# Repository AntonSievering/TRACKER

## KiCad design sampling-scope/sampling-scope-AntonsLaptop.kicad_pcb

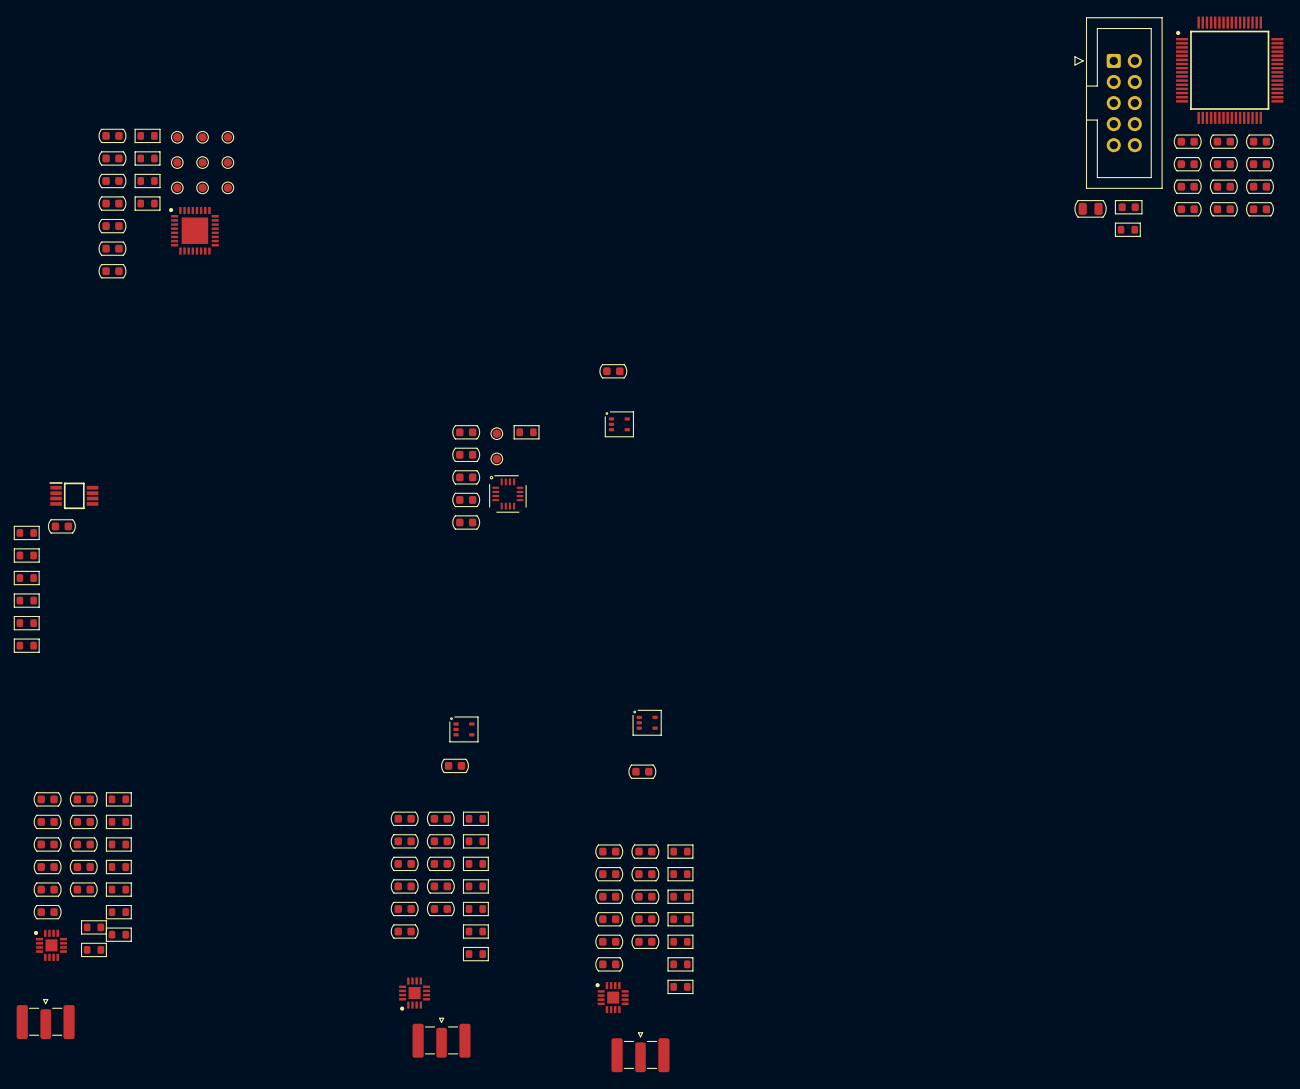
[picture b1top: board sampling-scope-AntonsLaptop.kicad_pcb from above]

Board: 4 copper layers, 123 parts (0 on the bottom side), 54 nets, no tracks yet.

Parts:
C1, C2, C7, C8, C11, C12, C13, C14, C15, C16, C19, C20, C21, C24, C25, C26, C27, C28, C29, C32, C36, C37, C38, C39, C44, C45, C46, C47, C48, C49, C54, C55, C56, C57, C58, C59, C62: 100n; C_0603_1608Metric
C3, C4, C5, C6, C33, C34, C35: 10n; C_0603_1608Metric
C9, C10, C17, C18, C22, C23, C30, C31, C43, C50, C51, C52, C53, C60, C61: 1u; C_0603_1608Metric
C40, C41: 2u2; C_0603_1608Metric
C42: 10u; C_0805_2012Metric
FB1: 1k@100MHz; L_0603_1608Metric
IC1: SY89296UMG; QFN50P500X500X90-33N-D
IC2, IC4, IC6: ADCMP582; QFN50P300X300X80-17N-D
IC3: SY10EP51VKG; SOP65P490X110-8N
IC5: STM32H562RGT6; QFP50P1200X1200X160-64N
J1, J2, J3: SMA; SMA_Edge_Mount
J4: Conn_02x05_Counter_Clockwise; IDC-Header_2x05_P2.54mm_Vertical
R1, R3, R6, R8, R10, R21, R23, R25, R30, R32, R34: 127; R_0603_1608Metric
R2, R4, R7, R9, R11, R22, R24, R26, R31, R33, R35: 82.5; R_0603_1608Metric
R5, R12, R13, R14, R15, R16, R17, R18, R19, R20, R28, R29: 0; R_0603_1608Metric
R27: 49R9; R_0603_1608Metric
TP1, TP2, TP3, TP4, TP5, TP6, TP7, TP8, TP9, TP10, TP11: TestPoint; TestPoint_Pad_D1.0mm
U1, U2, U4: LMV331; SOT-353_SC-70-5
U3: SY89831U; QFN-16_3x3mm_P0.5mm

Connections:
+3.3V: C1.1, C2.1, C3.1, C4.1, C5.1, C6.1, C7.1, C8.1, C15.1, C16.1, C18.1, C19.1, C20.1, C21.1, C28.1, C29.1, C31.1, C32.1, C33.1, C34.1, C35.1, C36.1, C37.1, C38.1, C42.1, C43.1, C44.1, C45.1, C46.1, C47.1, C48.1, C50.1, C58.1, C59.1, C61.1, C62.1, FB1.2, IC1.13 (VCC), IC1.18 (VCC), IC1.19 (VCC), IC1.22 (VCC), IC2.9 (V_{CCO}), IC2.12 (V_{CCO}), IC3.8 (VCC), IC4.9 (V_{CCO}), IC4.12 (V_{CCO}), IC5.1 (VBAT), IC5.19 (VDD_1), IC5.32 (VDD_2), IC5.48 (VDD_3), IC5.64 (VDD_4), IC6.9 (V_{CCO}), IC6.12 (V_{CCO}), R1.1, R3.1, R6.1, R8.1, R10.1, R12.1, R15.1, R21.1, R23.1, R25.1, R30.1, R32.1, R34.1, U1.5 (V+), U2.5 (V+), U3.7 (VCC), U3.14 (VCC), U4.5 (V+)
+5VA: C10.1, C12.1, C14.1, C23.1, C25.1, C27.1, C53.1, C55.1, C57.1, IC2.5 (VCCI), IC2.16 (VCCI), IC4.5 (VCCI), IC4.16 (VCCI), IC6.5 (VCCI), IC6.16 (VCCI)
-5VA: C9.1, C11.1, C13.1, C22.1, C24.1, C26.1, C52.1, C54.1, C56.1, IC2.13 (V_{EE}), IC4.13 (V_{EE}), IC6.13 (V_{EE})
/Clock Fanout 1:4/IN+: IC1.20 (~Q), U3.12 (IN)
/Clock Fanout 1:4/IN-: IC1.21 (Q), U3.9 (~IN)
/Microcontroller/DEBUG_RX: IC5.43 (PA10), J4.9
/Microcontroller/DEBUG_TX: IC5.42 (PA9), J4.10
/Microcontroller/JTCK: IC5.49 (PA14), J4.5
/Microcontroller/JTDI: IC5.50 (PA15), J4.3
/Microcontroller/JTDO: IC5.55 (PB3), J4.4
/Microcontroller/JTMS: IC5.46 (PA13), J4.6
/Microcontroller/NRST: C39.1, IC5.7 (NRST), J4.8
/Microcontroller/boot0_r: IC5.60 (BOOT0), R28.2
/Microcontroller/stm32_vdda: C49.1, C51.1, FB1.1, IC5.13 (VDDA)
/Microcontroller/stm_vcap1: C40.1, IC5.30 (VCAP_1)
/Microcontroller/stm_vcap2: C41.1, IC5.62 (VCAP_2)
/Sampling Head CH1/High Speed Comparator/COMP_OUT+: IC4.11 (Q), R23.2, R24.1, U2.1 (+)
/Sampling Head CH1/High Speed Comparator/COMP_OUT-: IC4.10 (~Q), R25.2, R26.1, U2.3 (-)
/Sampling Head CH1/SIGNAL: IC4.2 (VP), J2.1 (In)
/Sampling Head CH2/High Speed Comparator/COMP_OUT+: IC6.11 (Q), R32.2, R33.1, U4.1 (+)
/Sampling Head CH2/High Speed Comparator/COMP_OUT-: IC6.10 (~Q), R34.2, R35.1, U4.3 (-)
/Sampling Head CH2/SIGNAL: IC6.2 (VP), J3.1 (In)
/Trigger Circuitry/Delay Line/IN+: IC1.4 (IN), R1.2, R2.1, R18.2
/Trigger Circuitry/Delay Line/IN-: IC1.5 (~IN), R3.2, R4.1, R19.2
/Trigger Circuitry/High Speed Comparator/CMP_LE+: IC2.7 (LE), R12.2
/Trigger Circuitry/High Speed Comparator/CMP_LE-: IC2.6 (~LE), R13.2
/Trigger Circuitry/High Speed Comparator/COMP_OUT+: IC2.11 (Q), R8.2, R9.1, R16.1
/Trigger Circuitry/High Speed Comparator/COMP_OUT-: IC2.10 (~Q), R10.2, R11.1, R17.1
/Trigger Circuitry/TRIG: IC2.2 (VP), J1.1 (In)
GND: C1.2, C2.2, C3.2, C4.2, C5.2, C6.2, C7.2, C8.2, C9.2, C10.2, C11.2, C12.2, C13.2, C14.2, C15.2, C16.2, C17.2, C18.2, C19.2, C20.2, C21.2, C22.2, C23.2, C24.2, C25.2, C26.2, C27.2, C28.2, C29.2, C30.2, C31.2, C32.2, C34.2, C35.2, C36.2, C37.2, C38.2, C39.2, C40.2, C41.2, C42.2, C43.2, C44.2, C45.2, C46.2, C47.2, C48.2, C49.2, C50.2, C51.2, C52.2, C53.2, C54.2, C55.2, C56.2, C57.2, C58.2, C59.2, C60.2, C61.2, C62.2, IC1.9 (GND), IC1.24 (GND), IC1.28 (GND), IC1.33 (EP), IC2.1 (VTP), IC2.15 (GND), IC2.17 (EP), IC3.5 (GND), IC4.1 (VTP), IC4.15 (GND), IC4.17 (EP), IC5.12 (VSSA), IC5.18 (VSS_1), IC5.31 (VSS_2), IC5.47 (VSS_3), IC5.63 (VSS_4), IC6.1 (VTP), IC6.15 (GND), IC6.17 (EP), J1.2 (Ext), J2.2 (Ext), J3.2 (Ext), J4.2, J4.7, R2.2, R4.2, R7.2, R9.2, R11.2, R13.1, R22.2, R24.2, R26.2, R27.2, R28.1, R31.2, R33.2, R35.2, U1.2 (V-), U2.2 (V-), U3.13 (GND), U4.2 (V-)
unnamed: IC1.15 (CASCADE), TP5.1
unnamed: IC1.3 (D10), TP1.1
unnamed: IC1.12 (SETMAX), TP3.1
unnamed: IC1.11 (SETMIN), TP2.1
unnamed: IC1.6 (VBB), TP9.1
unnamed: IC1.8 (VCF), TP7.1
unnamed: IC1.7 (VEF), TP8.1
unnamed: IC1.14 (~CASCADE), TP6.1
unnamed: IC1.16 (~EN), TP4.1
unnamed: IC2.3 (VN), IC2.4 (VTN), R5.2
unnamed: C17.1, IC2.8 (V_{TT}), R6.2, R7.1
unnamed: IC3.3 (CLK), R16.2
unnamed: IC3.2 (D), R15.2
unnamed: IC3.7 (Q), R18.1
unnamed: IC3.1 (RESET), R14.2
unnamed: IC3.4 (~CLK), R17.2
unnamed: IC3.6 (~Q), R19.1
unnamed: IC4.3 (VN), IC4.4 (VTN), R20.2
unnamed: C30.1, IC4.8 (V_{TT}), R21.2, R22.1
unnamed: IC6.3 (VN), IC6.4 (VTN), R29.2
unnamed: C60.1, IC6.8 (V_{TT}), R30.2, R31.1
unnamed: TP11.1, U3.8 (RESET)
unnamed: TP10.1, U3.10 (VREF-AC)
unnamed: C33.2, R27.1, U3.11 (VT)

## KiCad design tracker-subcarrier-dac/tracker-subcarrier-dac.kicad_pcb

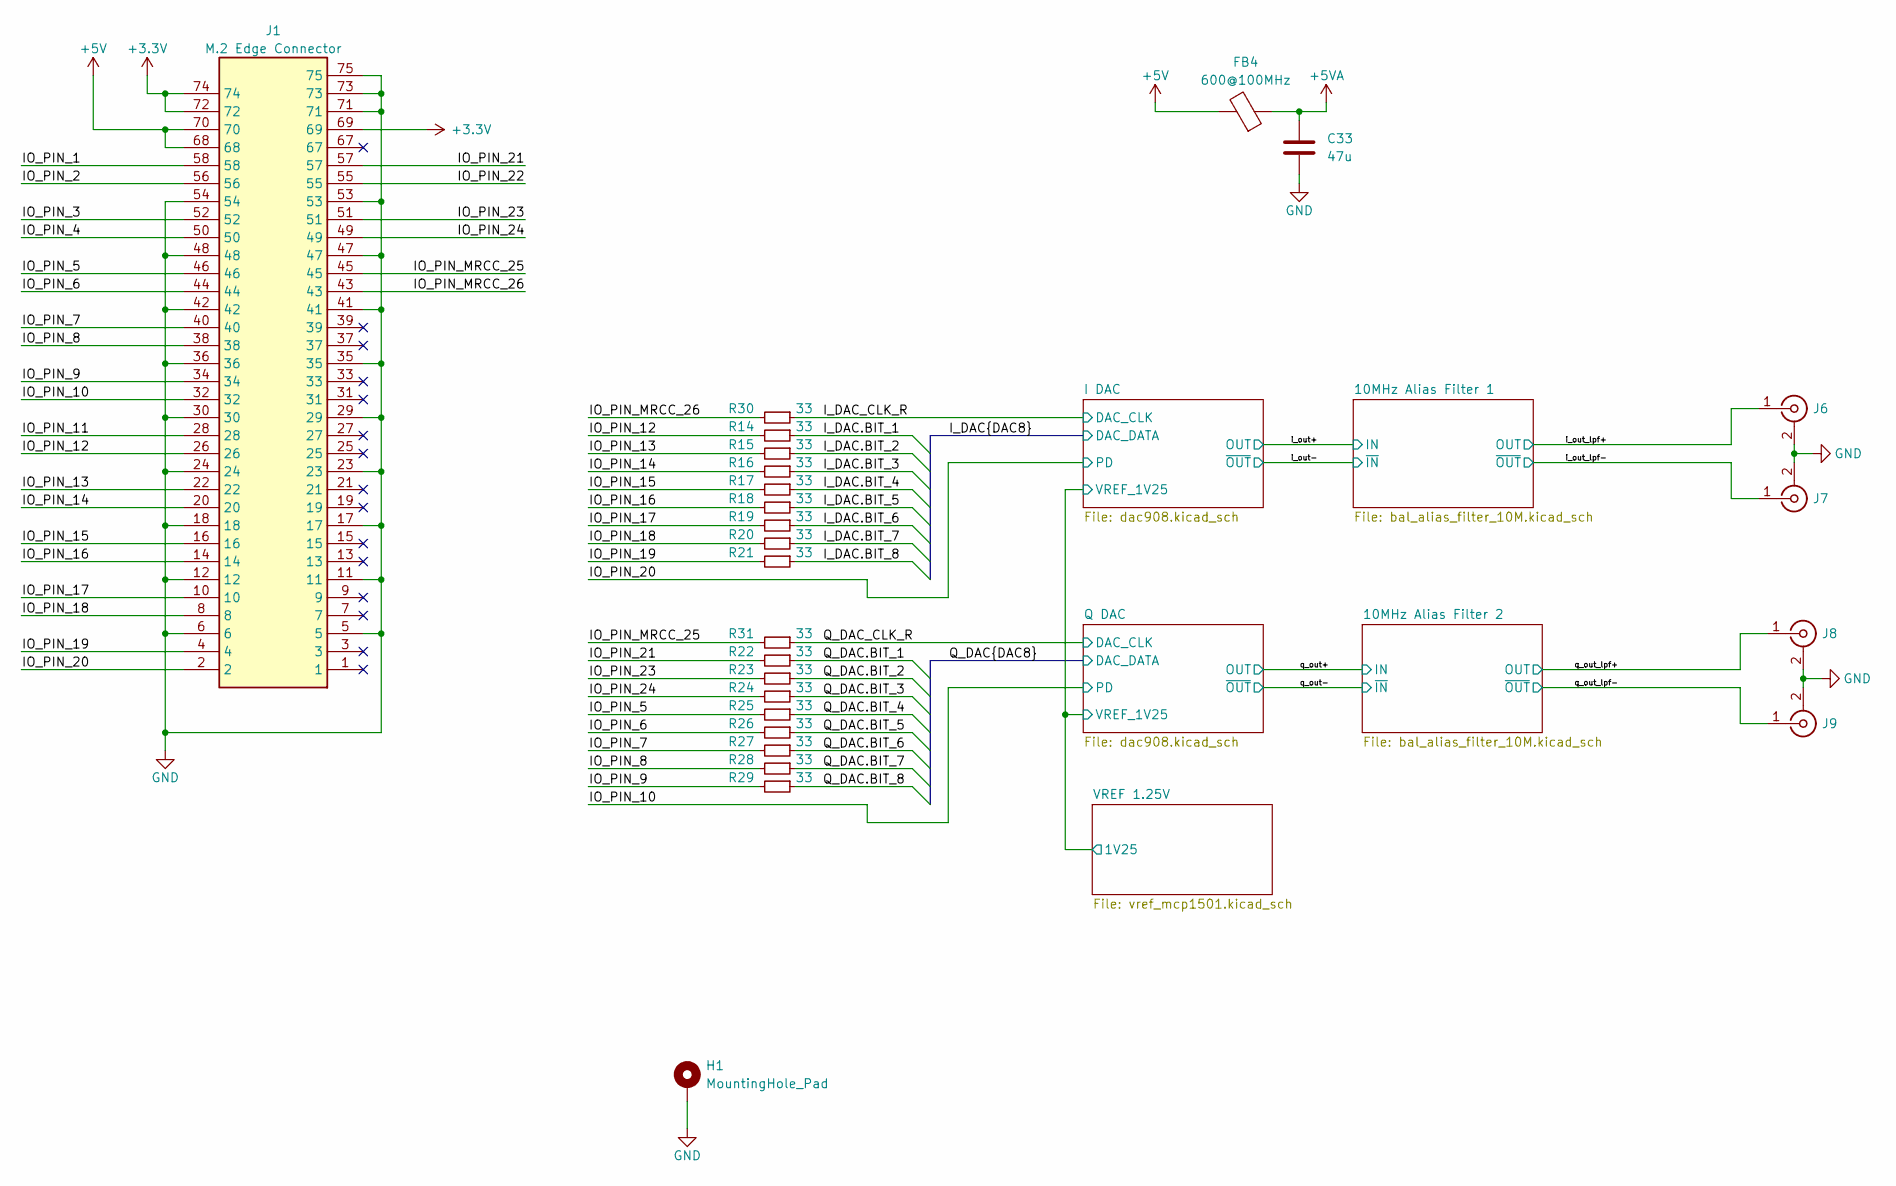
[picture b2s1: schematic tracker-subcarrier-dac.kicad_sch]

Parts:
C33: 47u; C_0805_2012Metric
FB4: 600@100MHz; L_0805_2012Metric
H1: MountingHole_Pad; MountingHole_2.5mm_Pad
J1: M.2 Edge Connector; M.2_2242-xx-M
J6, J7, J8, J9: Conn_Coaxial; SMA_Amphenol_901-144_Vertical
R14, R15, R16, R17, R18, R19, R20, R21, R22, R23, R24, R25, R26, R27, R28, R29, R30, R31: 33; R_0603_1608Metric; MPN RC0603FR-1033RL

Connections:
+3.3V: J1.69, J1.72, J1.74; also elsewhere on the board
+5V: FB4.2, J1.68, J1.70
+5VA: C33.1, FB4.1; also elsewhere on the board
/IO_PIN_1: J1.58
/IO_PIN_2: J1.56
/IO_PIN_3: J1.52
/IO_PIN_4: J1.50
/IO_PIN_5: J1.46, R25.2
/IO_PIN_6: J1.44, R26.2
/IO_PIN_7: J1.40, R27.2
/IO_PIN_8: J1.38, R28.2
/IO_PIN_9: J1.34, R29.2
/IO_PIN_10: J1.32; also elsewhere on the board
/IO_PIN_11: J1.28
/IO_PIN_12: J1.26, R14.2
/IO_PIN_13: J1.22, R15.2
/IO_PIN_14: J1.20, R16.2
/IO_PIN_15: J1.16, R17.2
/IO_PIN_16: J1.14, R18.2
/IO_PIN_17: J1.10, R19.2
/IO_PIN_18: J1.8, R20.2
/IO_PIN_19: J1.4, R21.2
/IO_PIN_20: J1.2; also elsewhere on the board
/IO_PIN_21: J1.57, R22.2
/IO_PIN_22: J1.55
/IO_PIN_23: J1.51, R23.2
/IO_PIN_24: J1.49, R24.2
/IO_PIN_MRCC_25: J1.45, R31.2
/IO_PIN_MRCC_26: J1.43, R30.2
/I_DAC.BIT_1: R14.1; also elsewhere on the board
/I_DAC.BIT_2: R15.1; also elsewhere on the board
/I_DAC.BIT_3: R16.1; also elsewhere on the board
/I_DAC.BIT_4: R17.1; also elsewhere on the board
/I_DAC.BIT_5: R18.1; also elsewhere on the board
/I_DAC.BIT_6: R19.1; also elsewhere on the board
/I_DAC.BIT_7: R20.1; also elsewhere on the board
/I_DAC.BIT_8: R21.1; also elsewhere on the board
/I_DAC_CLK_R: R30.1; also elsewhere on the board
/Q_DAC.BIT_1: R22.1; also elsewhere on the board
/Q_DAC.BIT_2: R23.1; also elsewhere on the board
/Q_DAC.BIT_3: R24.1; also elsewhere on the board
/Q_DAC.BIT_4: R25.1; also elsewhere on the board
/Q_DAC.BIT_5: R26.1; also elsewhere on the board
/Q_DAC.BIT_6: R27.1; also elsewhere on the board
/Q_DAC.BIT_7: R28.1; also elsewhere on the board
/Q_DAC.BIT_8: R29.1; also elsewhere on the board
/Q_DAC_CLK_R: R31.1; also elsewhere on the board
/i_out_lpf+: J6.1 (In); also elsewhere on the board
/i_out_lpf-: J7.1 (In); also elsewhere on the board
/q_out_lpf+: J8.1 (In); also elsewhere on the board
/q_out_lpf-: J9.1 (In); also elsewhere on the board
GND: C33.2, H1.1, J1.5, J1.6, J1.11, J1.12, J1.17, J1.18, J1.23, J1.24, J1.29, J1.30, J1.35, J1.36, J1.41, J1.42, J1.47, J1.48, J1.53, J1.54, J1.71, J1.73, J1.75, J6.2 (Ext), J7.2 (Ext), J8.2 (Ext), J9.2 (Ext); also elsewhere on the board

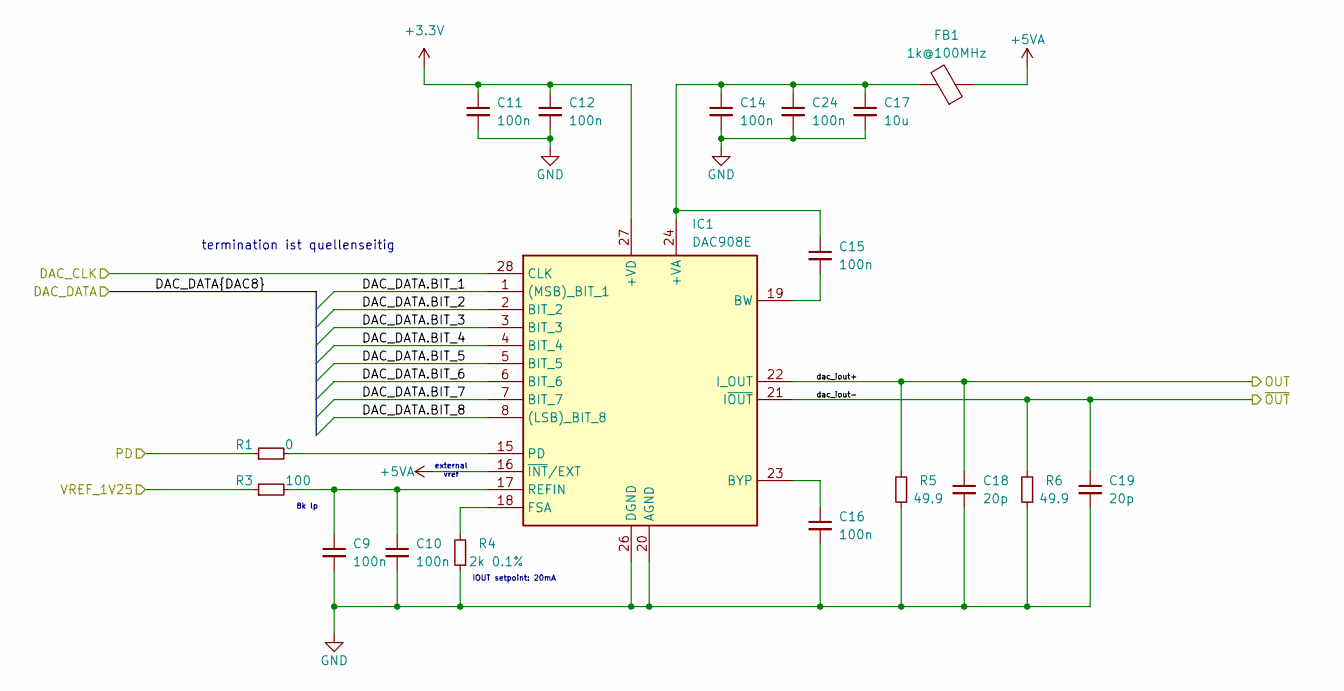
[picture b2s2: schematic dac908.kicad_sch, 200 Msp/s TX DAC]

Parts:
C9, C10, C15: 100n; C_0603_1608Metric
C11, C12, C14, C16, C24: 100n; C_0402_1005Metric
C17: 10u; C_0805_2012Metric
C18, C19: 20p; C_0603_1608Metric
FB1: 1k@100MHz; L_0603_1608Metric; MPN 81-BLM18KG102SH1D
IC1: DAC908E; SOP65P640X120-28N; Mouser Part Number 595-DAC908E
R1: 0; R_0603_1608Metric
R3: 100; R_0603_1608Metric
R4: 2k 0.1%; R_0603_1608Metric; MPN RT0603BRD072KL
R5, R6: 49.9; R_0603_1608Metric

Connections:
+3.3V: C11.1, C12.1, IC1.27 (+VD); also elsewhere on the board
+5VA: FB1.1, IC1.16 (~INT/EXT); also elsewhere on the board
/I DAC/VREF_1V25: R3.1; also elsewhere on the board
/IO_PIN_20: R1.1; also elsewhere on the board
/I_DAC.BIT_1: IC1.1 ((MSB)_BIT_1); also elsewhere on the board
/I_DAC.BIT_2: IC1.2 (BIT_2); also elsewhere on the board
/I_DAC.BIT_3: IC1.3 (BIT_3); also elsewhere on the board
/I_DAC.BIT_4: IC1.4 (BIT_4); also elsewhere on the board
/I_DAC.BIT_5: IC1.5 (BIT_5); also elsewhere on the board
/I_DAC.BIT_6: IC1.6 (BIT_6); also elsewhere on the board
/I_DAC.BIT_7: IC1.7 (BIT_7); also elsewhere on the board
/I_DAC.BIT_8: IC1.8 ((LSB)_BIT_8); also elsewhere on the board
/I_DAC_CLK_R: IC1.28 (CLK); also elsewhere on the board
/i_out+: C18.1, IC1.22 (I_OUT), R5.2; also elsewhere on the board
/i_out-: C19.1, IC1.21 (I~OUT), R6.2; also elsewhere on the board
GND: C9.2, C10.2, C11.2, C12.2, C14.2, C16.2, C17.2, C18.2, C19.2, C24.2, IC1.9 (NC_1), IC1.10 (NC_2), IC1.11 (NC_3), IC1.12 (NC_4), IC1.13 (NC_5), IC1.14 (NC_6), IC1.20 (AGND), IC1.26 (DGND), R4.1, R5.1, R6.1; also elsewhere on the board
unnamed: C14.1, C15.1, C17.1, C24.1, FB1.2, IC1.24 (+VA)
unnamed: C15.2, IC1.19 (BW)
unnamed: C16.1, IC1.23 (BYP)
unnamed: IC1.18 (FSA), R4.2
unnamed: IC1.15 (PD), R1.2
unnamed: C9.1, C10.1, IC1.17 (REFIN), R3.2

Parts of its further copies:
C13, C22, C23, C25, C27: 100n; C_0402_1005Metric
C20, C21, C26: 100n; C_0603_1608Metric
C28: 10u; C_0805_2012Metric
C29, C30: 20p; C_0603_1608Metric
FB2: 1k@100MHz; L_0603_1608Metric; MPN 81-BLM18KG102SH1D
IC2: DAC908E; SOP65P640X120-28N; Mouser Part Number 595-DAC908E
R7: 0; R_0603_1608Metric
R9: 100; R_0603_1608Metric
R10: 2k 0.1%; R_0603_1608Metric; MPN RT0603BRD072KL
R11, R12: 49.9; R_0603_1608Metric

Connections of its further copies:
+3.3V: C13.1, C22.1, IC2.27 (+VD); also elsewhere on the board
+5VA: FB2.1, IC2.16 (~INT/EXT); also elsewhere on the board
/I DAC/VREF_1V25: R9.1; also elsewhere on the board
/IO_PIN_10: R7.1; also elsewhere on the board
/Q_DAC.BIT_1: IC2.1 ((MSB)_BIT_1); also elsewhere on the board
/Q_DAC.BIT_2: IC2.2 (BIT_2); also elsewhere on the board
/Q_DAC.BIT_3: IC2.3 (BIT_3); also elsewhere on the board
/Q_DAC.BIT_4: IC2.4 (BIT_4); also elsewhere on the board
/Q_DAC.BIT_5: IC2.5 (BIT_5); also elsewhere on the board
/Q_DAC.BIT_6: IC2.6 (BIT_6); also elsewhere on the board
/Q_DAC.BIT_7: IC2.7 (BIT_7); also elsewhere on the board
/Q_DAC.BIT_8: IC2.8 ((LSB)_BIT_8); also elsewhere on the board
/Q_DAC_CLK_R: IC2.28 (CLK); also elsewhere on the board
/q_out+: C29.1, IC2.22 (I_OUT), R11.2; also elsewhere on the board
/q_out-: C30.1, IC2.21 (I~OUT), R12.2; also elsewhere on the board
GND: C13.2, C20.2, C21.2, C22.2, C23.2, C25.2, C27.2, C28.2, C29.2, C30.2, IC2.9 (NC_1), IC2.10 (NC_2), IC2.11 (NC_3), IC2.12 (NC_4), IC2.13 (NC_5), IC2.14 (NC_6), IC2.20 (AGND), IC2.26 (DGND), R10.1, R11.1, R12.1; also elsewhere on the board
unnamed: C23.1, C25.1, C26.1, C28.1, FB2.2, IC2.24 (+VA)
unnamed: C26.2, IC2.19 (BW)
unnamed: C27.1, IC2.23 (BYP)
unnamed: IC2.18 (FSA), R10.2
unnamed: IC2.15 (PD), R7.2
unnamed: C20.1, C21.1, IC2.17 (REFIN), R9.2

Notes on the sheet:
termination ist quellenseitig
external vref
8k lp
IOUT setpoint: 20mA

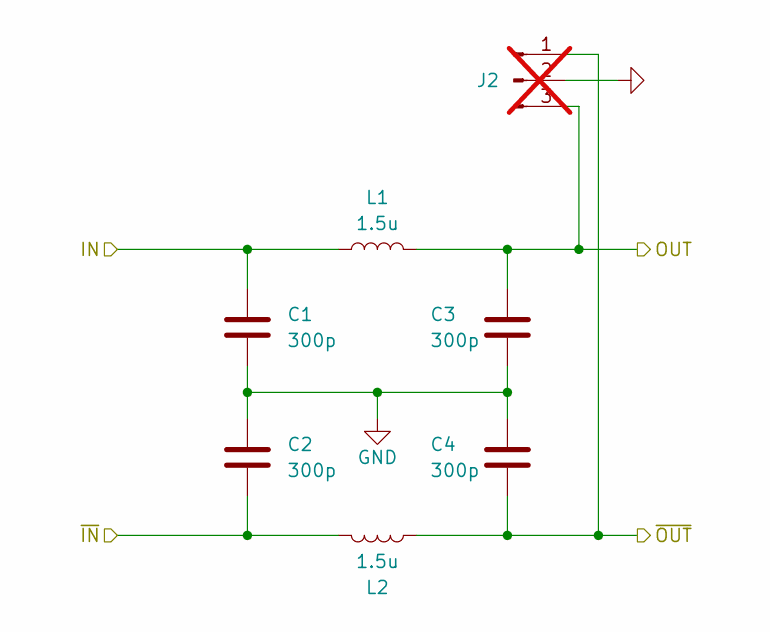
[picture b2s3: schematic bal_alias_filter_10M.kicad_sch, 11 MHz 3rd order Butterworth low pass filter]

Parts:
C1, C2, C3, C4: 300p; C_0603_1608Metric; MPN GCM1885C2A301FA16J
J2: Conn_01x03_Pin; PinHeader_1x03_P1.27mm_Vertical; not fitted
L1, L2: 1.5u; L_0603_1608Metric; MPN MLF1608A1R5JT000

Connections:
/i_out+: C1.1, L1.1; also elsewhere on the board
/i_out-: C2.2, L2.1; also elsewhere on the board
/i_out_lpf+: C3.1, J2.3, L1.2; also elsewhere on the board
/i_out_lpf-: C4.2, J2.1, L2.2; also elsewhere on the board
GND: C1.2, C2.1, C3.2, C4.1, J2.2; also elsewhere on the board

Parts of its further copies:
C5, C6, C7, C8: 300p; C_0603_1608Metric; MPN GCM1885C2A301FA16J
J3: Conn_01x03_Pin; PinHeader_1x03_P1.27mm_Vertical; not fitted
L3, L4: 1.5u; L_0603_1608Metric; MPN MLF1608A1R5JT000

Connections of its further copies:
/q_out+: C5.1, L3.1; also elsewhere on the board
/q_out-: C6.2, L4.1; also elsewhere on the board
/q_out_lpf+: C7.1, J3.3, L3.2; also elsewhere on the board
/q_out_lpf-: C8.2, J3.1, L4.2; also elsewhere on the board
GND: C5.2, C6.1, C7.2, C8.1, J3.2; also elsewhere on the board

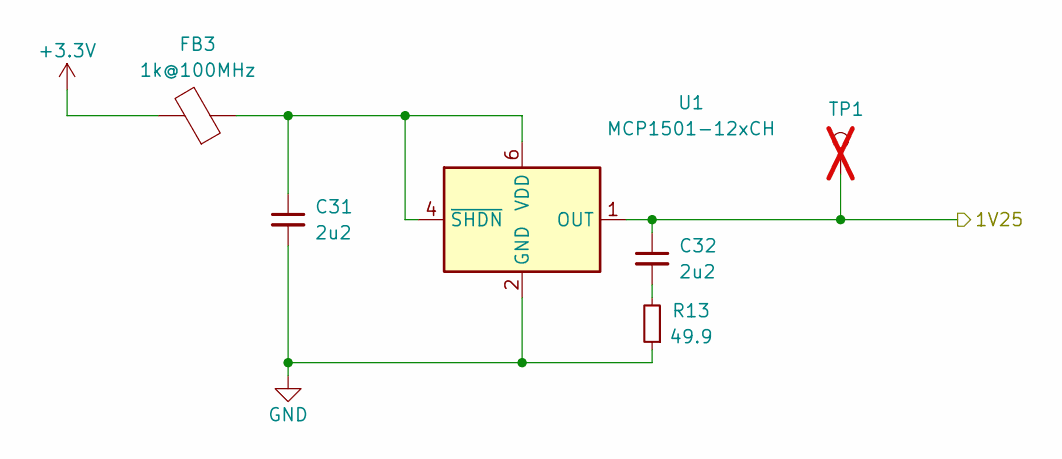
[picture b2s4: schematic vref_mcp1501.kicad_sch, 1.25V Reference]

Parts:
C31, C32: 2u2; C_0603_1608Metric
FB3: 1k@100MHz; L_0603_1608Metric; MPN 81-BLM18KG102SH1D
R13: 49.9; R_0603_1608Metric
TP1: TestPoint; Pin_D1.0mm_L10.0mm; not fitted
U1: MCP1501-12xCH; SOT-23-6; MPN MCP1501T-12E/CHY

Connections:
+3.3V: FB3.2; also elsewhere on the board
/I DAC/VREF_1V25: C32.1, TP1.1, U1.1 (OUT); also elsewhere on the board
GND: C31.2, R13.1, U1.2 (GND), U1.3 (GND), U1.5 (GND); also elsewhere on the board
unnamed: C32.2, R13.2
unnamed: C31.1, FB3.1, U1.4 (~SHDN), U1.6 (VDD)

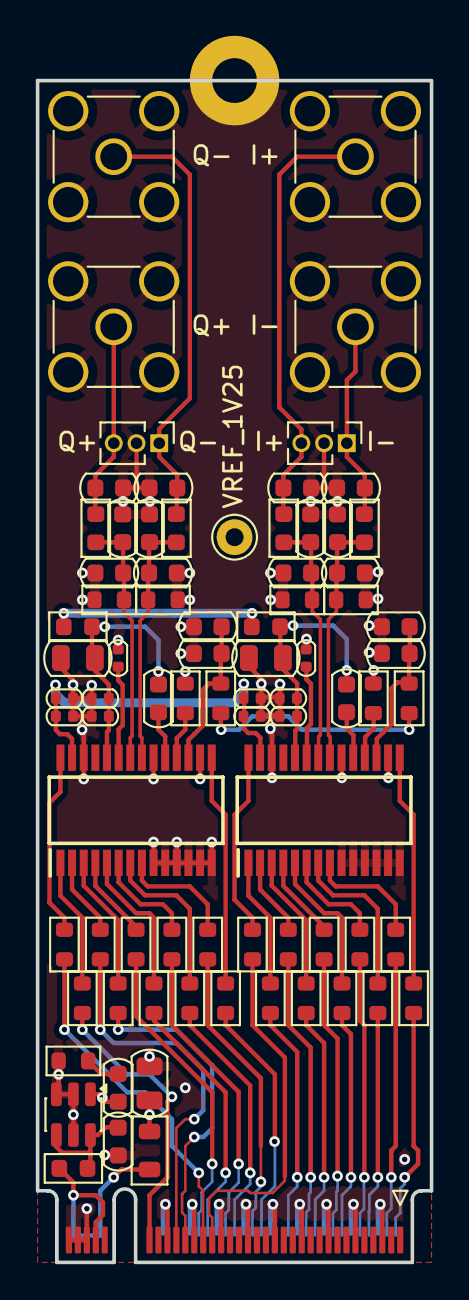
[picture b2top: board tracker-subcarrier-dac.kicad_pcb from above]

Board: 4 copper layers, 22.0 x 66.0 mm, 82 parts (0 on the bottom side), 65 nets.

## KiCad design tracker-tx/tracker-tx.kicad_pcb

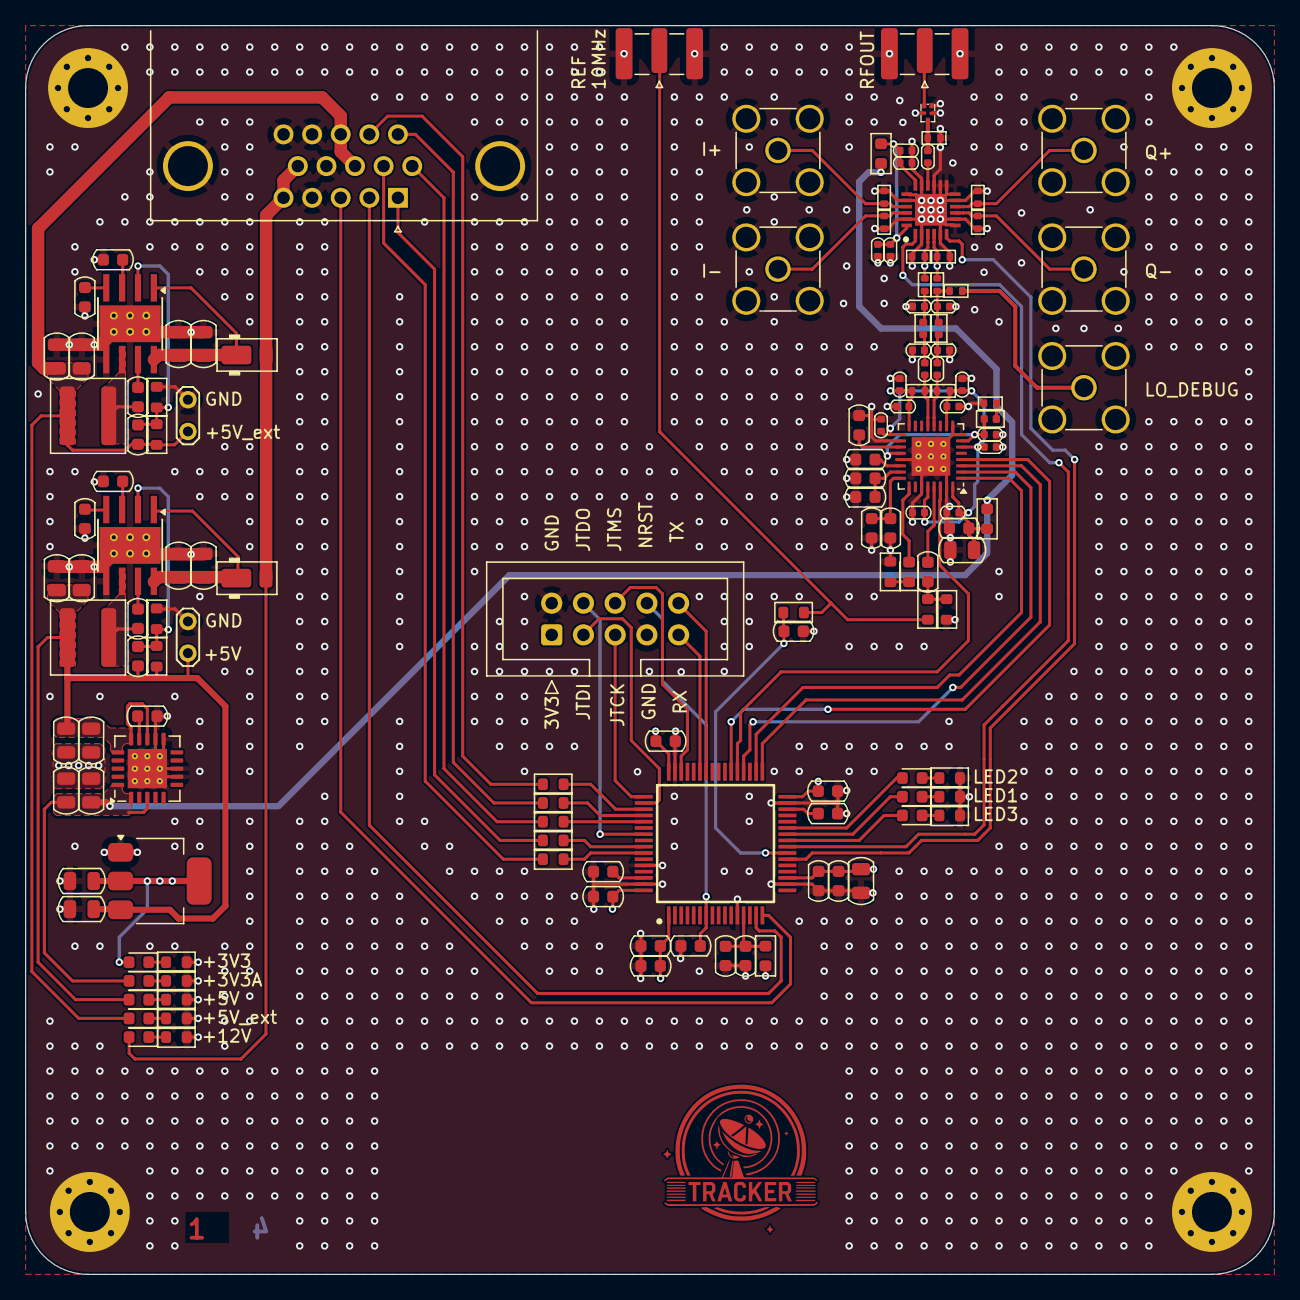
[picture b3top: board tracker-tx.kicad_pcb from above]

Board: 4 copper layers, 100.0 x 100.0 mm, 142 parts (0 on the bottom side), 89 nets.

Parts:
C1, C6, C15, C28, C33, C34, C35, C36, C37, C38, C46, C50: 100n; C_0603_1608Metric
C1_LF1, C60, C61, C62, C63: 1n; C_0402_1005Metric
C2_LF1: 6.8n; L_0402_1005Metric
C3, C10, C11, C19, C30, C42, C43, C45, C80, C82: 10u; C_0805_2012Metric
C4, C13, C32, C39, C40, C86: 1u; C_0603_1608Metric
C5, C14: 3.3n; C_0603_1608Metric
C7, C16: 100p; C_0603_1608Metric
C8, C9, C17, C18: 22u; C_0805_2012Metric
C29, C31: 2u2; C_0603_1608Metric
C47, C48, C49, C51, C52, C53: 100p; C_0402_1005Metric
C54: 2.2u; C_0603_1608Metric
C55, C58: 22u; C_0603_1608Metric
C56, C57, C59: 10u; C_0603_1608Metric
C64, C65, C66, C67: 1p; C_0402_1005Metric
C69, C70, C71, C72: 100n; C_0402_1005Metric
C73: 6.8p; C_0402_1005Metric
C87, C90: 47u; C_0805_2012Metric
D1, D2, D3, D4: LED; D_0603_1608Metric
D5, D10: DFLS130; D_PowerDI-123
D6, D7, D8, D9, D11: LED; LED_0603_1608Metric
FB3, FB4, FB5: 1k@100MHz; L_0603_1608Metric
H1, H2, H3, H4: MountingHole_Pad; MountingHole_3.2mm_M3_Pad_Via
IC3: STM32H562RGT6; QFP50P1200X1200X160-64N
IC4: LMX2581SQE_NOPB; QFN-32-1EP_5x5mm_P0.5mm_EP3.1x3.1mm_ThermalVias
IC5: TRF37T05IRGET; QFN50P400X400X100-25N-D
J1, J4: Conn_Coaxial; SMA_Edge_Mount
J2, J3, J6, J7, J9: Conn_Coaxial; SMA_Amphenol_901-144_Vertical
J5: DA15_Socket_MountingHoles; DSUB-15-HD_Pins_Horizontal_P2.29x2.54mm_EdgePinOffset8.35mm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
J8: Conn_02x05_Counter_Clockwise; IDC-Header_2x05_P2.54mm_Vertical
L1, L2: 3.3u; L_Coilcraft_XAL5030
L5, L6: 5.1n; L_0402_1005Metric
R1, R6, R7, R8, R16, R17, R18, R21, R29, R35, R37, R38: 10k; R_0603_1608Metric
R2, R3, R32, R52: 0; R_0402_1005Metric
R2_LF1: 820R; R_0402_1005Metric
R4, R5: 56k; R_0603_1608Metric
R19: 0; R_0603_1608Metric
R20: 49.9; R_0603_1608Metric
R22, R23, R24, R25, R26, R27, R28, R31: 49.9; R_0402_1005Metric
R46, R47, R49, R50, R51: 33; R_0603_1608Metric
TP1, TP3: TestPoint_2Pole; TestPoint_2Pads_Pitch2.54mm_Drill0.8mm
U1: AFS14A72-2436.00-T3; AFS14A72
U2, U5: BD9D321EFJ; Texas_HTSOP-8-1EP_3.9x4.9mm_P1.27mm_EP2.95x4.9mm_Mask2.4x3.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
U3: LM1117MP-3.3; SOT-223-3_TabPin2
U4: TPS7A4701xRGW; Texas_RGW0020A_VQFN-20-1EP_5x5mm_P0.65mm_EP3.15x3.15mm_Ther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

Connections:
+3.3V: C3.1, C30.1, C32.1, C33.1, C34.1, C35.1, C36.1, C37.1, C39.1, D8.2 (A), FB3.2, IC3.1 (VBAT), IC3.19 (VDD_1), IC3.32 (VDD_2), IC3.48 (VDD_3), IC3.64 (VDD_4), J8.1, U3.2 (VO)
+3.3VA: C87.1, C90.1, D9.2 (A), FB4.2, FB5.1, U4.1 (OUT), U4.3 (SENSE/FB), U4.20 (OUT)
+5V: C7.1, C8.1, C9.1, C19.1, C80.1, C82.1, D6.2 (A), L2.2, R4.1, TP3.1, U3.3 (VI), U4.13 (EN), U4.15 (IN), U4.16 (IN)
+5V_ext: C16.1, C17.1, C18.1, D11.2 (A), J5.8, J5.13, L1.2, R5.1, TP1.1
+12V: D5.2 (A), D7.2 (A), D10.2 (A), J5.5, J5.10
/IL_MISO: J5.6, R49.1
/IL_MOSI: J5.11 (P111), R50.1
/IL_RX: J5.1, R47.1
/IL_SCK: J5.12, R51.1
/IL_TX: J5.7, R46.1
/MOD_GAIN_CONTROL: IC3.22 (PA6), IC5.6 (GC)
/MOD_POWER_DOWN: IC3.24 (PC4), IC5.1 (PD)
/Microcontroller/DEBUG_RX: IC3.43 (PA10), J8.9
/Microcontroller/DEBUG_TX: IC3.42 (PA9), J8.10
/Microcontroller/JTCK: IC3.49 (PA14), J8.5
/Microcontroller/JTDI: IC3.50 (PA15), J8.3
/Microcontroller/JTDO: IC3.55 (PB3), J8.4
/Microcontroller/JTMS: IC3.46 (PA13), J8.6
/Microcontroller/LED1: D1.2 (A), IC3.26 (PB0)
/Microcontroller/LED2: D2.2 (A), IC3.27 (PB1)
/Microcontroller/LED3: D3.2 (A), IC3.25 (PC5)
/Microcontroller/NRST: C28.1, IC3.7 (NRST), J8.8
/Microcontroller/PB5: IC3.57 (PB5), R47.2
/Microcontroller/PB6: IC3.58 (PB6), R46.2
/Microcontroller/PC10: IC3.51 (PC10), R51.2
/Microcontroller/PC11: IC3.52 (PC11), R50.2
/Microcontroller/PC12: IC3.53 (PC12), R49.2
/Microcontroller/stm32_vdda: C38.1, C40.1, FB3.1, IC3.13 (VDDA)
/Microcontroller/stm_vcap1: C29.1, IC3.30 (VCAP_1)
/Microcontroller/stm_vcap2: C31.1, IC3.62 (VCAP_2)
/PLL_CE: IC3.38 (PC7), IC4.4 (CE)
/PLL_CLK: IC3.34 (PB13), IC4.1 (CLK)
/PLL_DATA: IC3.36 (PB15), IC4.2 (DATA)
/PLL_LE: IC3.33 (PB12), IC4.3 (LE)
/PLL_MUXOUT: IC3.37 (PC6), IC4.30 (MUXOUT)
/Power Supply/sw_1: C6.2, L2.1, U5.6 (SW)
/Power Supply/sw_2: C15.2, L1.1, U2.6 (SW)
/Power Supply/v_supply_ext: C10.1, C11.1, D5.1 (K), U2.1 (EN), U2.8 (VIN)
/Power Supply/v_supply_int: C42.1, C43.1, D10.1 (K), U5.1 (EN), U5.8 (VIN)
/Quadrature Modulator/rfout_c_50r: C73.1, IC5.16 (RFOUT)
/REF_AVAIL: C1.1, IC3.23 (PA7), R1.2
/STM_GPIO_1: IC3.15 (PA1), J5.2
/STM_GPIO_2: IC3.16 (PA2), J5.3
/TX PLL/f_{refin}: J1.1 (In), R1.1, R19.1
/TX PLL/pll_3v3: C45.1, C46.1, C47.1, C48.1, C49.1, C51.1, C52.1, C53.1, C60.1, C61.1, FB4.1, IC4.6 (VCCCP), IC4.10 (VCCPLL), IC4.16 (VCCBUF), IC4.17 (VCCVCO), IC4.28 (VCCDIG), IC4.32 (VCCFRAC), R22.1, R23.1
/TX PLL/pll_lpf_int+: C62.2, C64.1, L5.1
/TX PLL/pll_lpf_int-: C63.2, C65.2, L6.1
/TX PLL/pll_rfout+: C62.1, IC4.12 (RFOUTA+), R23.2
/TX PLL/pll_rfout-: C63.1, IC4.13 (RFOUTA-), R22.2
/i_out_lpf+: IC5.21 (BBIP), J2.1 (In), R28.2
/i_out_lpf-: IC5.22 (BBIM), J3.1 (In), R31.2
/lo_out_50r: J9.1 (In), R3.2
/mod_lo+: IC5.3 (LOP), R2.1, R24.2
/mod_lo-: IC5.4 (LOM), R25.2, R52.1
/mod_out_50r: C73.2, R32.2, U1.C (in)
/pll_lo+: C66.1, L5.2, R3.1, R52.2
/pll_lo-: C67.2, L6.2, R2.2
/q_out_lpf+: IC5.10 (BBQP), J6.1 (In), R26.2
/q_out_lpf-: IC5.9 (BBQM), J7.1 (In), R27.2
/rfout_bp_50r: J4.1 (In), U1.A (out)
GND: C1.2, C1_LF1.2, C3.2, C4.2, C5.2, C8.2, C9.2, C10.2, C11.2, C13.2, C14.2, C17.2, C18.2, C19.2, C28.2, C29.2, C30.2, C31.2, C32.2, C33.2, C34.2, C35.2, C36.2, C37.2, C38.2, C39.2, C40.2, C42.2, C43.2, C45.2, C46.2, C47.2, C48.2, C49.2, C51.2, C52.2, C53.2, C54.2, C55.2, C56.2, C57.2, C58.2, C59.2, C60.2, C61.2, C64.2, C65.1, C66.2, C67.1, C69.2, C70.2, C71.2, C72.2, C80.2, C82.2, C86.2, C87.2, C90.2, H1.1, H2.1, H3.1, H4.1, IC3.12 (VSSA), IC3.18 (VSS_1), IC3.31 (VSS_2), IC3.47 (VSS_3), IC3.60 (BOOT0), IC3.63 (VSS_4), IC4.8 (GND_1), IC4.9 (GND_2), IC4.18 (GND_3), IC4.21 (GND_4), IC4.27 (GND_5), IC4.31 (GND_6), IC4.33 (EP), IC5.2 (GND_1), IC5.5 (GND_2), IC5.7 (GND_3), IC5.8 (GND_4), IC5.11 (GND_5), IC5.12 (GND_6), IC5.13 (GND_7), IC5.14 (GND_8), IC5.15 (GND_9), IC5.17 (GND_10), IC5.19 (GND_11), IC5.20 (GND_12), IC5.23 (GND_13), IC5.25 (EP), J1.2 (Ext), J2.2 (Ext), J3.2 (Ext), J4.2 (Ext), J5.0 (PAD), J5.4, J5.9, J5.14, J5.15, J6.2 (Ext), J7.2 (Ext), J8.2, J8.7, J9.2 (Ext), R2_LF1.2, R6.2, R7.2, R8.2, R16.2, R17.2, R18.2, R20.2, R21.2, R24.1, R25.1, R26.1, R27.1, R28.1, R29.2, R31.1, R32.1, R35.2, R37.2, R38.2, TP1.2, TP3.2, U1.B (GND), U1.D (GND), U1.E (GND), U2.5 (GND), U2.9 (GND), U3.1 (GND), U4.7 (GND), U4.8 (1.6V), U4.11 (0.2V), U4.12 (0.1V), U4.21 (EP), U5.5 (GND), U5.9 (GND)
unnamed: C2_LF1.2, R2_LF1.1
unnamed: C50.1, R19.2, R20.1
unnamed: D1.1 (K), R16.1
unnamed: D2.1 (K), R17.1
unnamed: D3.1 (K), R18.1
unnamed: D4.2 (A), IC4.25 (LD)
unnamed: D4.1 (K), R21.1
unnamed: D6.1 (K), R35.1
unnamed: D7.1 (K), R7.1
unnamed: D8.1 (K), R37.1
unnamed: D9.1 (K), R38.1
unnamed: D11.1 (K), R8.1
unnamed: C1_LF1.1, C2_LF1.1, IC4.7 (CPOUT), IC4.20 (VTUNE)
unnamed: C50.2, IC4.29 (OSCIN)
unnamed: C58.1, C59.1, IC4.23 (VBIASCOMP)
unnamed: C57.1, IC4.19 (VBIASVCO)
unnamed: C54.1, IC4.22 (VREFVCO)
unnamed: C55.1, C56.1, IC4.24 (VREGVCO)
unnamed: C69.1, C70.1, C71.1, C72.1, FB5.2, IC5.18 (VCC_1), IC5.24 (VCC_2)
unnamed: C15.1, U2.7 (BOOT)
unnamed: C16.2, R5.2, R6.1, U2.2 (FB)
unnamed: C14.1, U2.4 (SS)
unnamed: C13.1, U2.3 (VREG)
unnamed: C86.1, U4.14 (NR)
unnamed: C6.1, U5.7 (BOOT)
unnamed: C7.2, R4.2, R29.1, U5.2 (FB)
unnamed: C5.1, U5.4 (SS)
unnamed: C4.1, U5.3 (VREG)
